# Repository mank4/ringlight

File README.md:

# Ringlight

ringlight is a LED ringlight for the Wild M3B stereo microscope. It it is mounted using the objective and does not stick out from the shape of the Wild M3B. ringlight requires 2 PCBs, one for the control and one aluminum core PCB (normal PCB should be also sufficient) for the LEDs. A spacer for mounting can be 3D printed.
The inner diameter of the LED PCB is chosen so that a photography polarization filter could be placed inside, but this is not tested. There are also mounting threads for a lens, intended to be 3D printed using clear resin with the option to mount a polarization filter foil onto the LED side. This is also not tested.

Feature:
- 24x Cree J Series 2835 high-CRI LEDs
- 10-step brightness control
- full circle, half circle and quarter circle modes with adjustable section size
- more configurations using SCPI pc-based control via USB

## RP2040 toolchain

Clone ringlight next to pico folder containing pico-examples, pico-sdk and picotool.

- Clone dependencies: `git submodule init` and `git submodule update`
- Create build folder in firmware and cd into. `cd fw && mkdir build && cd build`
- Then run `export PICO_SDK_PATH=../../../pico/pico-sdk` and `cmake ..`
- Then `make -j4`
- If compilation fails with USB descriptor length errors, do the following, cd into pico-sdk folder and `cd lib/tinyusb/` and then `git pull origin master`
- Then `../load.sh` with the RP2040 connected via USB. Press the button before pluggin in. (This is not needed when running the firmware. Make sure that picotool is build and you have set up the udev rules for the pico [udev rules](https://gist.github.com/alejoseb/c7a7b4c67f0cf665dadabb26a5a87597) and the ringlight:
```
/etc/udev/rules.d/99-ringlight.rules
SUBSYSTEMS=="usb", ACTION=="add", ATTRS{idVendor}=="16c0", ATTRS{idProduct}=="03e8",  MODE="0666", GROUP="usbtmc"
```

For details see the [Getting started](https://datasheets.raspberrypi.com/pico/getting-started-with-pico.pdf) guide.

## Resources

- Microcontroller
  - [RP2040](https://www.raspberrypi.com/documentation/microcontrollers/rp2040.html), [Pi pico](https://www.raspberrypi.com/products/raspberry-pi-pico/), RP2040 Minimal Kicad reference design
  - [SCPI specifications](https://www.ivifoundation.org/specifications/default.aspx), [SCPI-99 standard](https://www.ivifoundation.org/docs/scpi-99.pdf), [SCPI library](https://github.com/j123b567/scpi-parser)
  - [tinyusb for usbtmc](https://github.com/hathach/tinyusb), [example](https://github.com/markb139/pico_logic)

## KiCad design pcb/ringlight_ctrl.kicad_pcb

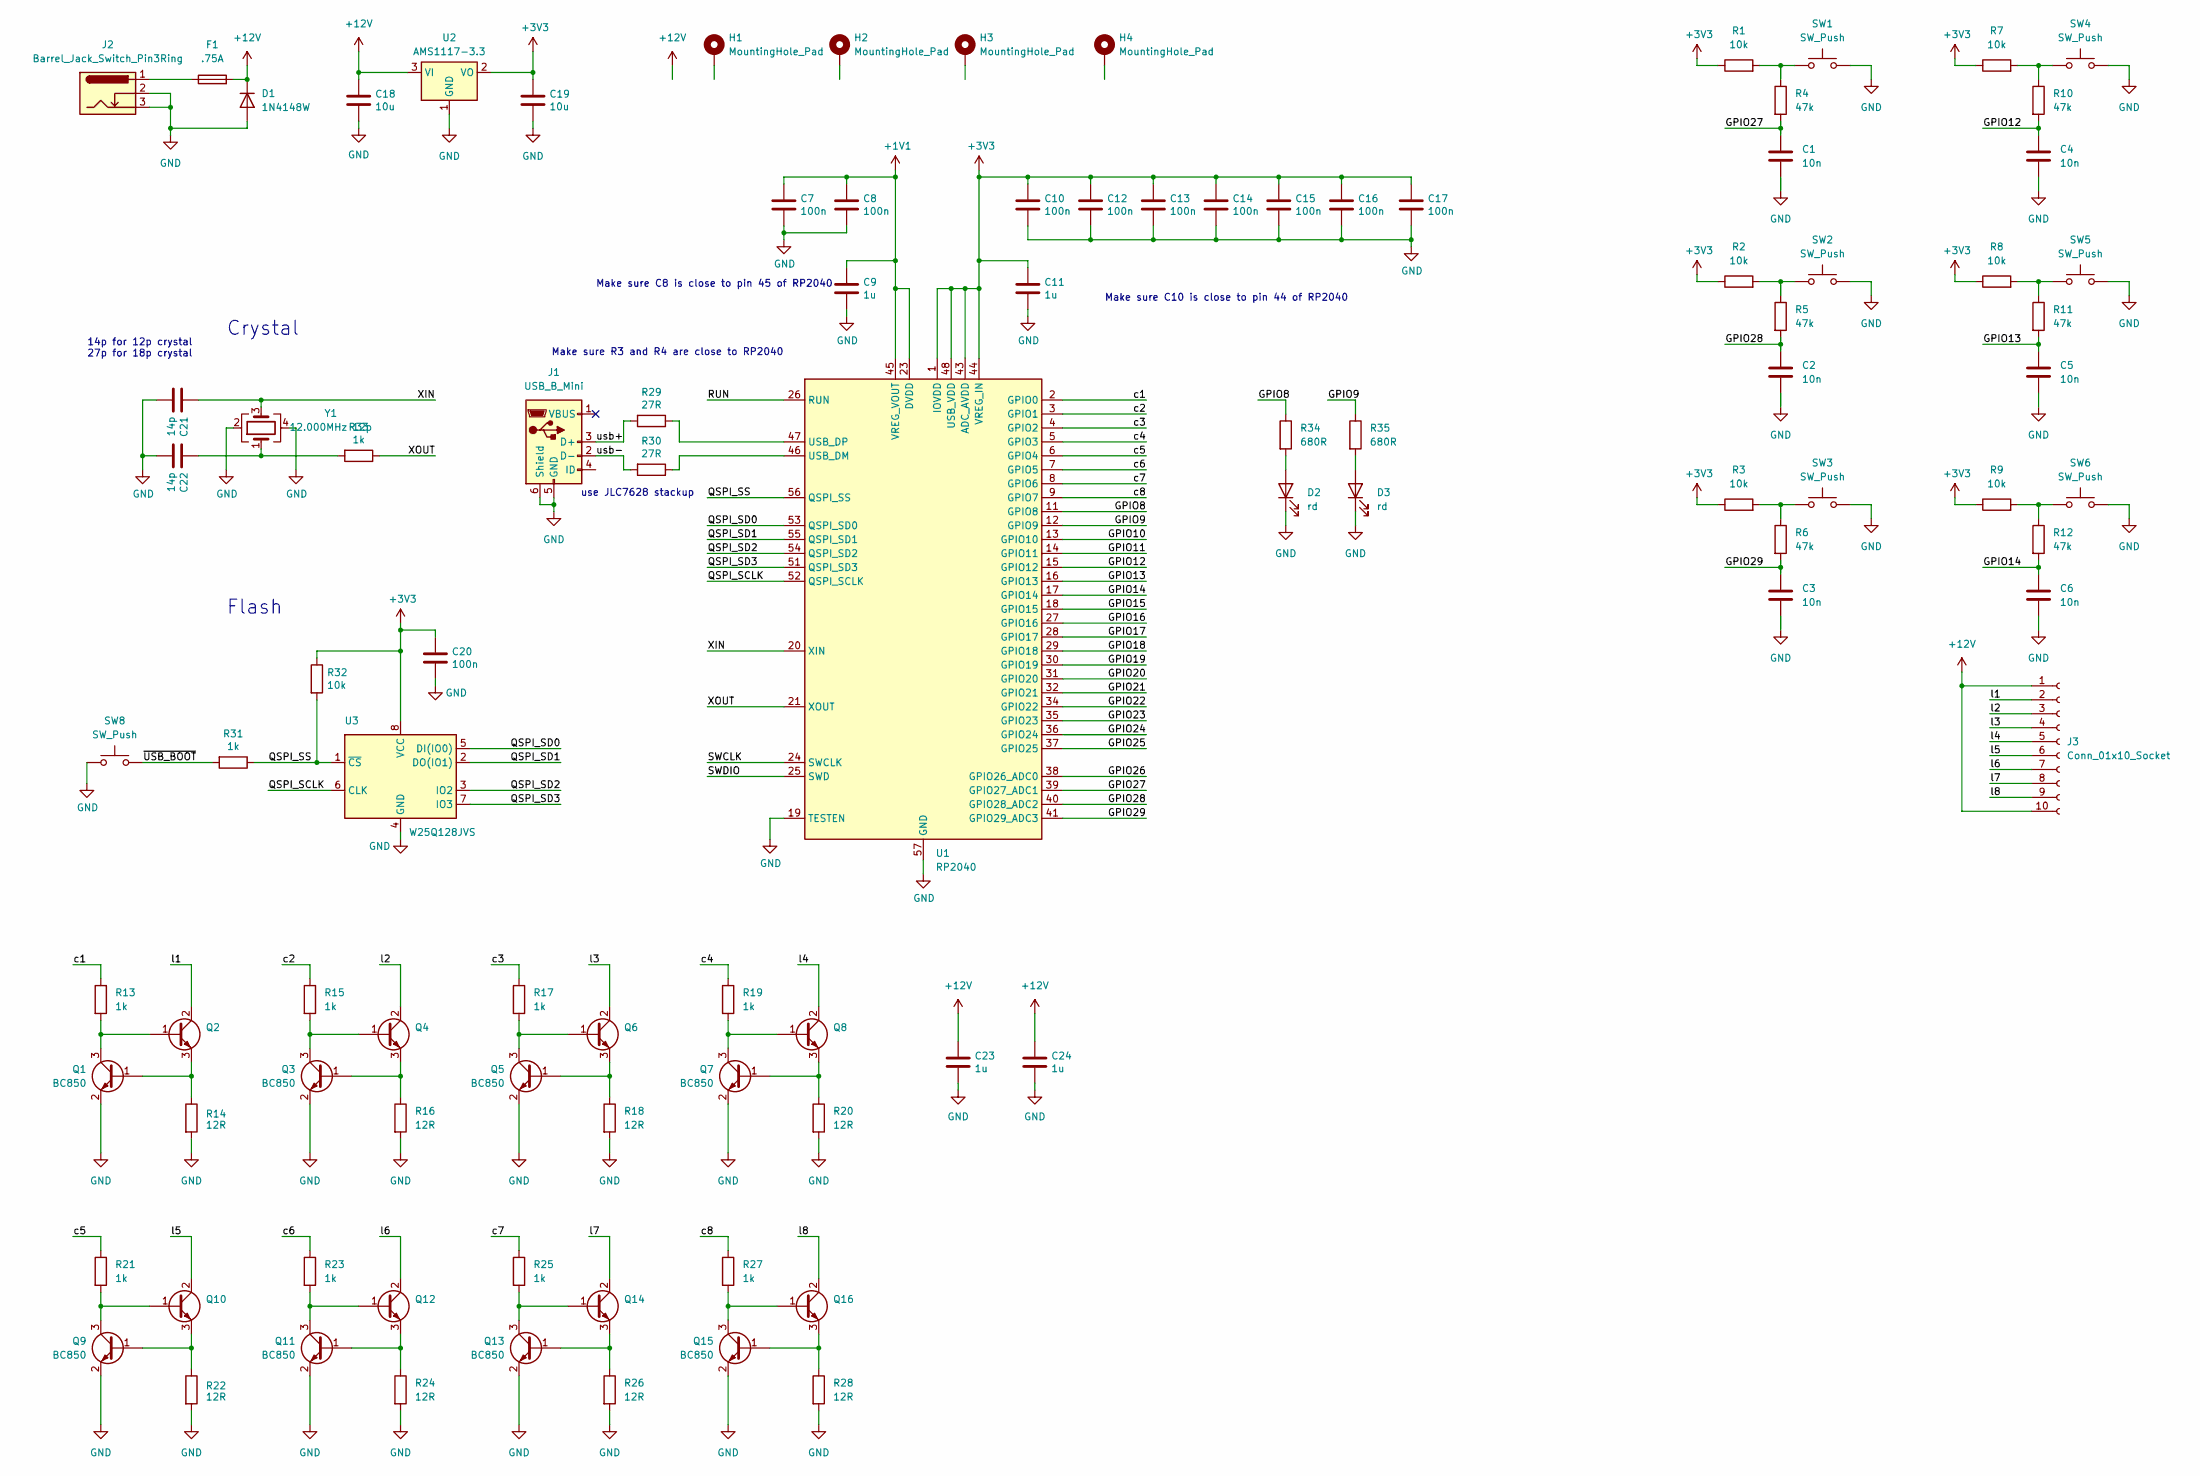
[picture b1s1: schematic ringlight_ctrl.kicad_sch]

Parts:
C1, C2, C3, C4, C5, C6: 10n; C_0805_2012Metric
C7, C8, C10, C12, C13, C14, C15, C16, C17, C20: 100n; C_0805_2012Metric
C9, C11, C23, C24: 1u; C_0805_2012Metric
C18, C19: 10u; C_0805_2012Metric
C21, C22: 14p; C_0805_2012Metric
D1: 1N4148W; D_SOD-123; Digikey 4878-1N4148WCT-ND
D2, D3: rd; LED_Kingbright_APA1606_1.6x0.6mm_Horizontal; Digikey 754-1054-1-ND
F1: .75A; Fuse_1206_3216Metric; Digikey 507-1805-1-ND
H1, H2, H3, H4: MountingHole_Pad; Mounting_Wuerth_WA-SMSI-M2_H8mm_9774080243; Digikey 732-7111-1-ND
J1: USB_B_Mini; USB_Mini-B_Wuerth_65100516121_Horizontal; Digikey 732-2109-1-ND
J2: Barrel_Jack_Switch_Pin3Ring; BarrelJack_CLIFF_FC681465S_SMT_Horizontal; Digikey 4654-FC681465S-ND
J3: Conn_01x10_Socket; conn_01x10
Q1, Q3, Q5, Q7, Q9, Q11, Q13, Q15: BC850; SOT-23; Digikey BC850BLT1GOSCT-ND
Q2, Q4, Q6, Q8, Q10, Q12, Q14, Q16: BCX56; SOT-89-3; Digikey 1727-2930-1-ND
R1, R2, R3, R7, R8, R9, R32: 10k; R_0805_2012Metric
R4, R5, R6, R10, R11, R12: 47k; R_0805_2012Metric
R13, R15, R17, R19, R21, R23, R25, R27, R31, R33: 1k; R_0805_2012Metric
R14, R16, R18, R20, R22, R24, R26, R28: 12R; R_0805_2012Metric
R29, R30: 27R; R_0805_2012Metric
R34, R35: 680R; R_0805_2012Metric
SW1, SW2, SW3, SW4, SW5, SW6: SW_Push; Panasonic_EVQPUL_EVQPUC; Digikey P10853SCT-ND
SW8: SW_Push; SW_Tactile_SPST_NO_Straight_CK_PTS636Sx25SMTRLFS; Digikey CKN12322-1-ND
U1: RP2040; QFN-56-1EP_7x7mm_P0.4mm_EP3.2x3.2mm; Digikey 2648-SC0914(13)CT-ND
U2: AMS1117-3.3; SOT-223-3_TabPin2
U3: W25Q128JVS; SOIC-8_5.23x5.23mm_P1.27mm; Digikey W25Q128JVSIQ-ND
Y1: 12.000MHz 12p; Crystal_SMD_Abracon_ABM3B-4Pin_5.0x3.2mm; Digikey 535-14827-1-ND

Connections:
+1V1: C7.1, C8.1, C9.1, U1.23 (DVDD), U1.45 (VREG_VOUT), U1.50 (DVDD)
+3V3: C10.1, C11.1, C12.1, C13.1, C14.1, C15.1, C16.1, C17.1, C19.1, C20.1, R1.1, R2.1, R3.1, R7.1, R8.1, R9.1, R32.1, U1.1 (IOVDD), U1.10 (IOVDD), U1.22 (IOVDD), U1.33 (IOVDD), U1.42 (IOVDD), U1.43 (ADC_AVDD), U1.44 (VREG_IN), U1.48 (USB_VDD), U1.49 (IOVDD), U2.2 (VO), U3.8 (VCC)
+12V: C18.1, C23.1, C24.1, D1.1 (K), F1.2, J3.1, J3.10, U2.3 (VI)
/GPIO8: R34.1, U1.11 (GPIO8)
/GPIO9: R35.1, U1.12 (GPIO9)
/GPIO10: U1.13 (GPIO10)
/GPIO11: U1.14 (GPIO11)
/GPIO12: C4.1, R10.2, U1.15 (GPIO12)
/GPIO13: C5.1, R11.2, U1.16 (GPIO13)
/GPIO14: C6.1, R12.2, U1.17 (GPIO14)
/GPIO15: U1.18 (GPIO15)
/GPIO16: U1.27 (GPIO16)
/GPIO17: U1.28 (GPIO17)
/GPIO18: U1.29 (GPIO18)
/GPIO19: U1.30 (GPIO19)
/GPIO20: U1.31 (GPIO20)
/GPIO21: U1.32 (GPIO21)
/GPIO22: U1.34 (GPIO22)
/GPIO23: U1.35 (GPIO23)
/GPIO24: U1.36 (GPIO24)
/GPIO25: U1.37 (GPIO25)
/GPIO26: U1.38 (GPIO26_ADC0)
/GPIO27: C1.1, R4.2, U1.39 (GPIO27_ADC1)
/GPIO28: C2.1, R5.2, U1.40 (GPIO28_ADC2)
/GPIO29: C3.1, R6.2, U1.41 (GPIO29_ADC3)
/QSPI_SCLK: U1.52 (QSPI_SCLK), U3.6 (CLK)
/QSPI_SD0: U1.53 (QSPI_SD0), U3.5 (DI(IO0))
/QSPI_SD1: U1.55 (QSPI_SD1), U3.2 (DO(IO1))
/QSPI_SD2: U1.54 (QSPI_SD2), U3.3 (IO2)
/QSPI_SD3: U1.51 (QSPI_SD3), U3.7 (IO3)
/QSPI_SS: R31.1, R32.2, U1.56 (QSPI_SS), U3.1 (~CS)
/RUN: U1.26 (RUN)
/SWCLK: U1.24 (SWCLK)
/SWDIO: U1.25 (SWD)
/XIN: C21.1, U1.20 (XIN), Y1.3
/XOUT: R33.1, U1.21 (XOUT)
/c1: R13.1, U1.2 (GPIO0)
/c2: R15.1, U1.3 (GPIO1)
/c3: R17.1, U1.4 (GPIO2)
/c4: R19.1, U1.5 (GPIO3)
/c5: R21.1, U1.6 (GPIO4)
/c6: R23.1, U1.7 (GPIO5)
/c7: R25.1, U1.8 (GPIO6)
/c8: R27.1, U1.9 (GPIO7)
/l1: J3.2, Q2.2 (C)
/l2: J3.3, Q4.2 (C)
/l3: J3.4, Q6.2 (C)
/l4: J3.5, Q8.2 (C)
/l5: J3.6, Q10.2 (C)
/l6: J3.7, Q12.2 (C)
/l7: J3.8, Q14.2 (C)
/l8: J3.9, Q16.2 (C)
/usb+: J1.3 (D+), R29.2
/usb-: J1.2 (D-), R30.2
/~USB_BOOT: R31.2, SW8.2
GND: C1.2, C2.2, C3.2, C4.2, C5.2, C6.2, C7.2, C8.2, C9.2, C10.2, C11.2, C12.2, C13.2, C14.2, C15.2, C16.2, C17.2, C18.2, C19.2, C20.2, C21.2, C22.2, C23.2, C24.2, D1.2 (A), D2.1 (K), D3.1 (K), J1.5 (GND), J1.6 (Shield), J2.2, J2.3, Q1.2 (E), Q3.2 (E), Q5.2 (E), Q7.2 (E), Q9.2 (E), Q11.2 (E), Q13.2 (E), Q15.2 (E), R14.2, R16.2, R18.2, R20.2, R22.2, R24.2, R26.2, R28.2, SW1.2, SW2.2, SW3.2, SW4.2, SW5.2, SW6.2, SW8.1, U1.19 (TESTEN), U1.57 (GND), U2.1 (GND), U3.4 (GND), Y1.2, Y1.4
unnamed: C22.1, R33.2, Y1.1
unnamed: D2.2 (A), R34.2
unnamed: D3.2 (A), R35.2
unnamed: F1.1, J2.1
unnamed: Q1.1 (B), Q2.3 (E), R14.1
unnamed: Q1.3 (C), Q2.1 (B), R13.2
unnamed: Q3.1 (B), Q4.3 (E), R16.1
unnamed: Q3.3 (C), Q4.1 (B), R15.2
unnamed: Q5.1 (B), Q6.3 (E), R18.1
unnamed: Q5.3 (C), Q6.1 (B), R17.2
unnamed: Q7.1 (B), Q8.3 (E), R20.1
unnamed: Q7.3 (C), Q8.1 (B), R19.2
unnamed: Q9.3 (C), Q10.1 (B), R21.2
unnamed: Q9.1 (B), Q10.3 (E), R22.1
unnamed: Q11.1 (B), Q12.3 (E), R24.1
unnamed: Q11.3 (C), Q12.1 (B), R23.2
unnamed: Q13.1 (B), Q14.3 (E), R26.1
unnamed: Q13.3 (C), Q14.1 (B), R25.2
unnamed: Q15.1 (B), Q16.3 (E), R28.1
unnamed: Q15.3 (C), Q16.1 (B), R27.2
unnamed: R1.2, R4.1, SW1.1
unnamed: R2.2, R5.1, SW2.1
unnamed: R3.2, R6.1, SW3.1
unnamed: R7.2, R10.1, SW4.1
unnamed: R8.2, R11.1, SW5.1
unnamed: R9.2, R12.1, SW6.1
unnamed: R30.1, U1.46 (USB_DM)
unnamed: R29.1, U1.47 (USB_DP)

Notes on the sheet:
Crystal
Make sure R3 and R4 are close to RP2040
14p for 12p crystal 27p for 18p crystal
Make sure C10 is close to pin 44 of RP2040
use JLC7628 stackup
Flash
Make sure C8 is close to pin 45 of RP2040

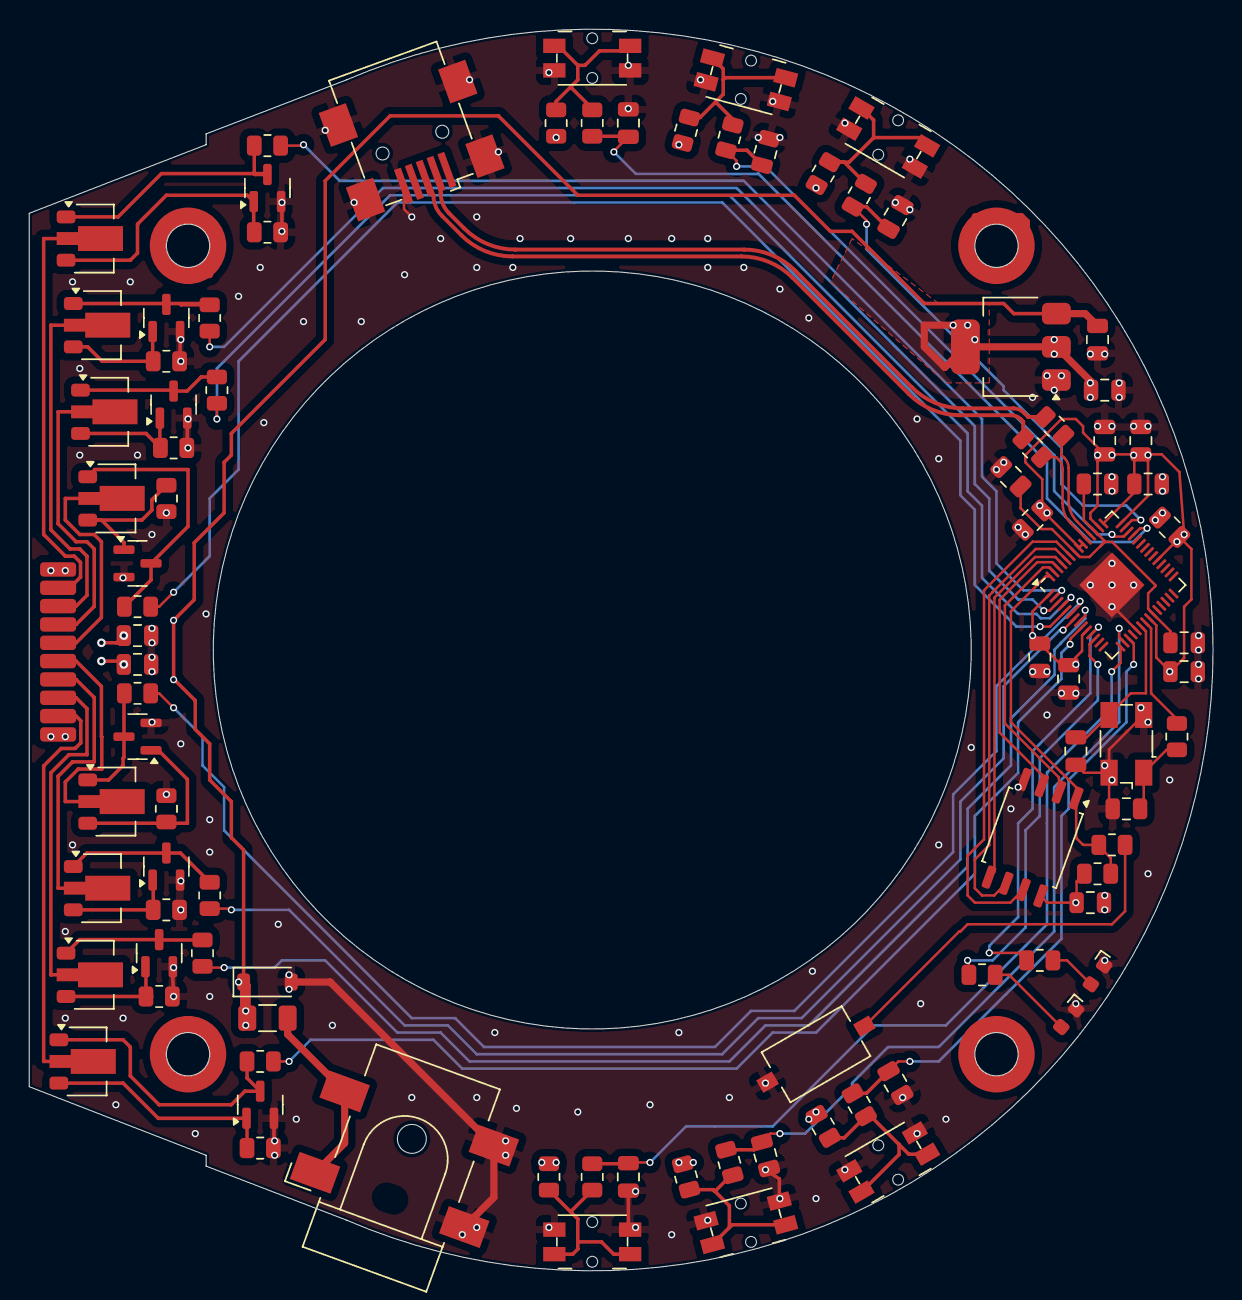
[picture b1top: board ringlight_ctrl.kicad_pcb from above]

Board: 4 copper layers, 82.0 x 86.0 mm, 97 parts (0 on the bottom side), 67 nets.

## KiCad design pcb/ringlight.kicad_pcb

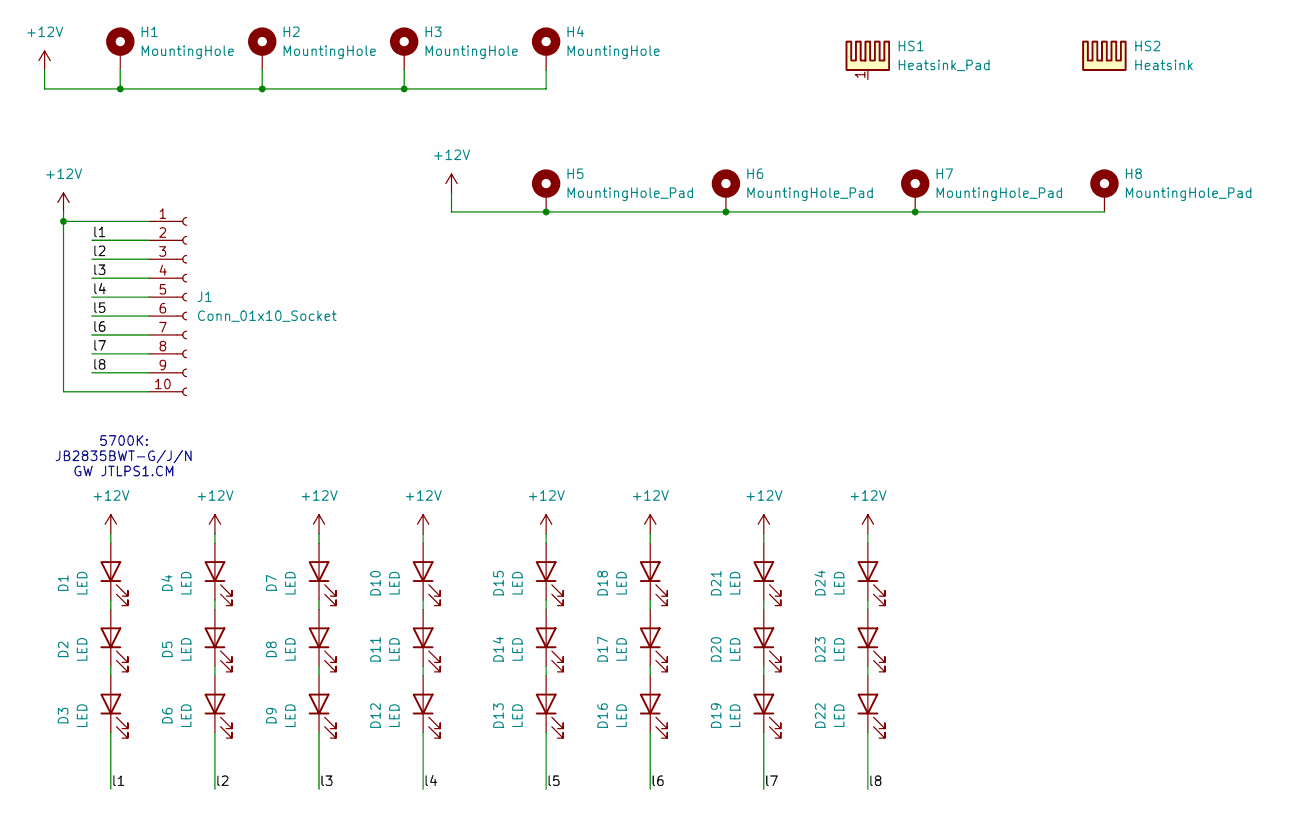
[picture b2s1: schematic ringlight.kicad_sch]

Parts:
D1, D2, D3, D4, D5, D6, D7, D8, D9, D10, D11, D12, D13, D14, D15, D16, D17, D18, D19, D20, D21, D22, D23, D24: LED; LED_PLCC_2835; Digikey 2138-JB2835BWT-G-U57EA0000-N000P001CT-ND
H1, H2, H3, H4: MountingHole; Mounting_Wuerth_WA-SMSI-M1.6_H1.5mm_9774015633; Digikey 732-13689-1-ND
H5, H6, H7, H8: MountingHole_Pad; MountingHole_2.2mm_M2_ISO14580_Pad
HS1: Heatsink_Pad; lens
HS2: Heatsink; filter
J1: Conn_01x10_Socket; conn_01x10

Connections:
+12V: D1.2 (A), D4.2 (A), D7.2 (A), D10.2 (A), D15.2 (A), D18.2 (A), D21.2 (A), D24.2 (A), H1.1, H2.1, H3.1, H4.1, H5.1, H6.1, H7.1, H8.1, J1.1, J1.10
/l1: D3.1 (K), J1.2
/l2: D6.1 (K), J1.3
/l3: D9.1 (K), J1.4
/l4: D12.1 (K), J1.5
/l5: D13.1 (K), J1.6
/l6: D16.1 (K), J1.7
/l7: D19.1 (K), J1.8
/l8: D22.1 (K), J1.9
unnamed: D1.1 (K), D2.2 (A)
unnamed: D2.1 (K), D3.2 (A)
unnamed: D4.1 (K), D5.2 (A)
unnamed: D5.1 (K), D6.2 (A)
unnamed: D7.1 (K), D8.2 (A)
unnamed: D8.1 (K), D9.2 (A)
unnamed: D10.1 (K), D11.2 (A)
unnamed: D11.1 (K), D12.2 (A)
unnamed: D13.2 (A), D14.1 (K)
unnamed: D14.2 (A), D15.1 (K)
unnamed: D16.2 (A), D17.1 (K)
unnamed: D17.2 (A), D18.1 (K)
unnamed: D19.2 (A), D20.1 (K)
unnamed: D20.2 (A), D21.1 (K)
unnamed: D22.2 (A), D23.1 (K)
unnamed: D23.2 (A), D24.1 (K)

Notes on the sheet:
5700K: JB2835BWT-G/J/N GW JTLPS1.CM

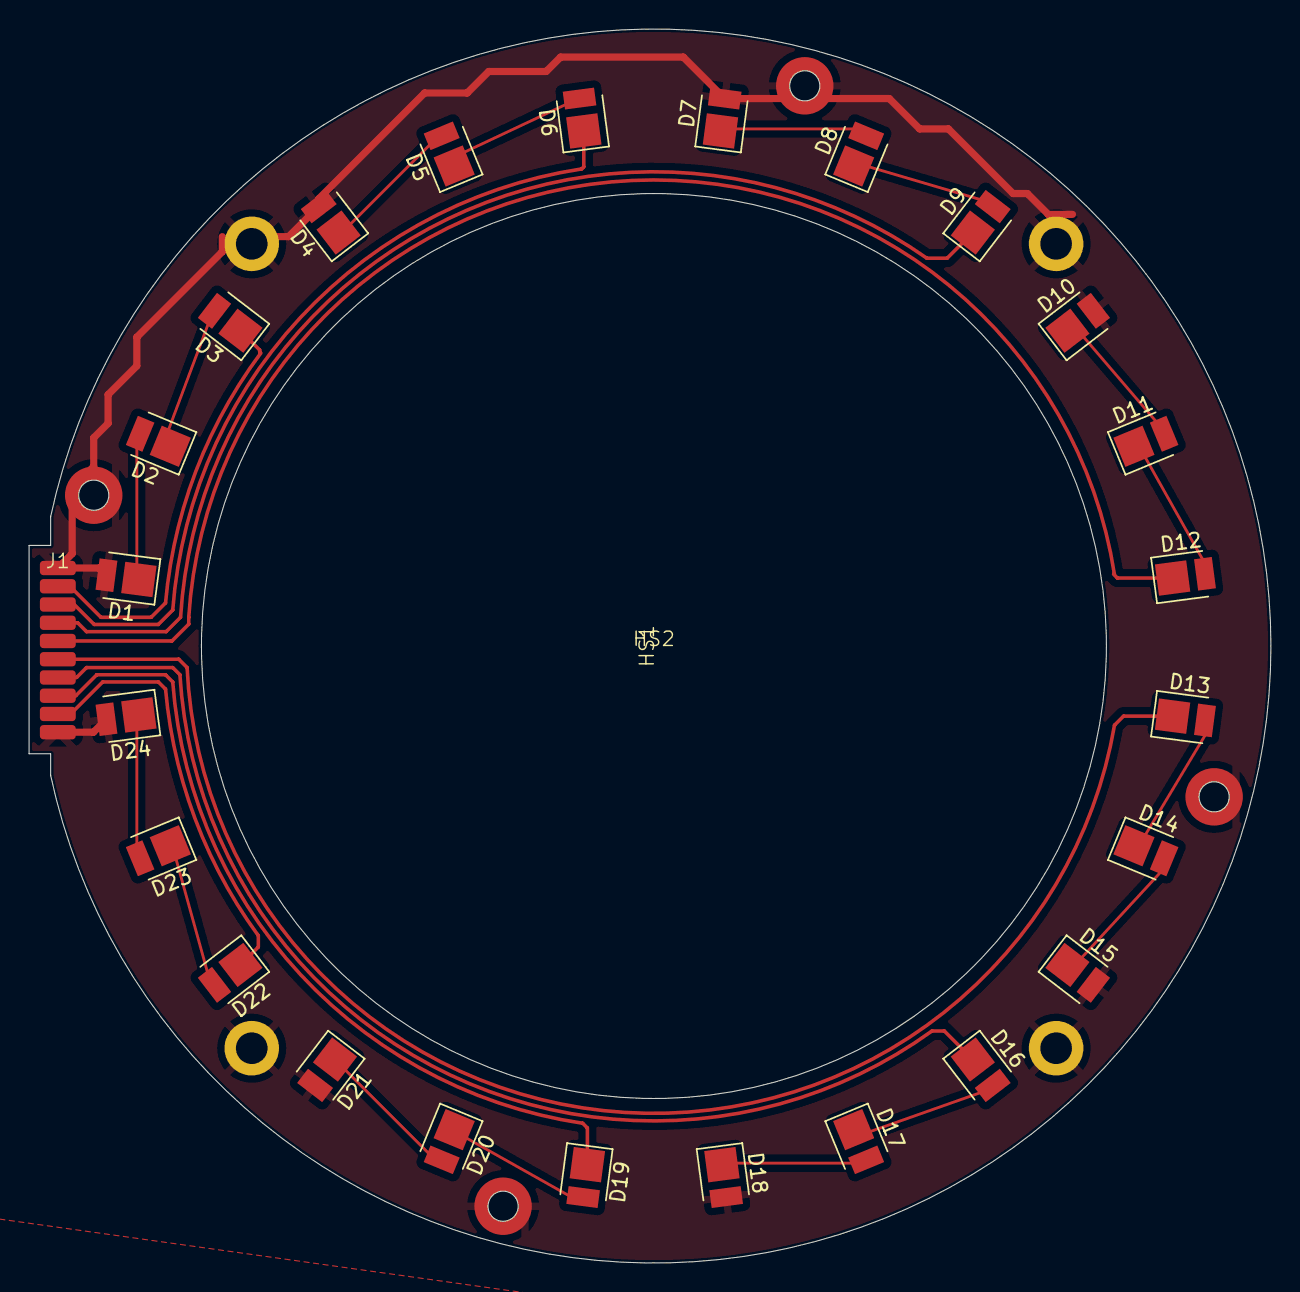
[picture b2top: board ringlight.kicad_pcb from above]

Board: 2 copper layers, 86.5 x 85.9 mm, 35 parts (0 on the bottom side), 25 nets.

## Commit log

2024-10-19 initial git version, design already built
